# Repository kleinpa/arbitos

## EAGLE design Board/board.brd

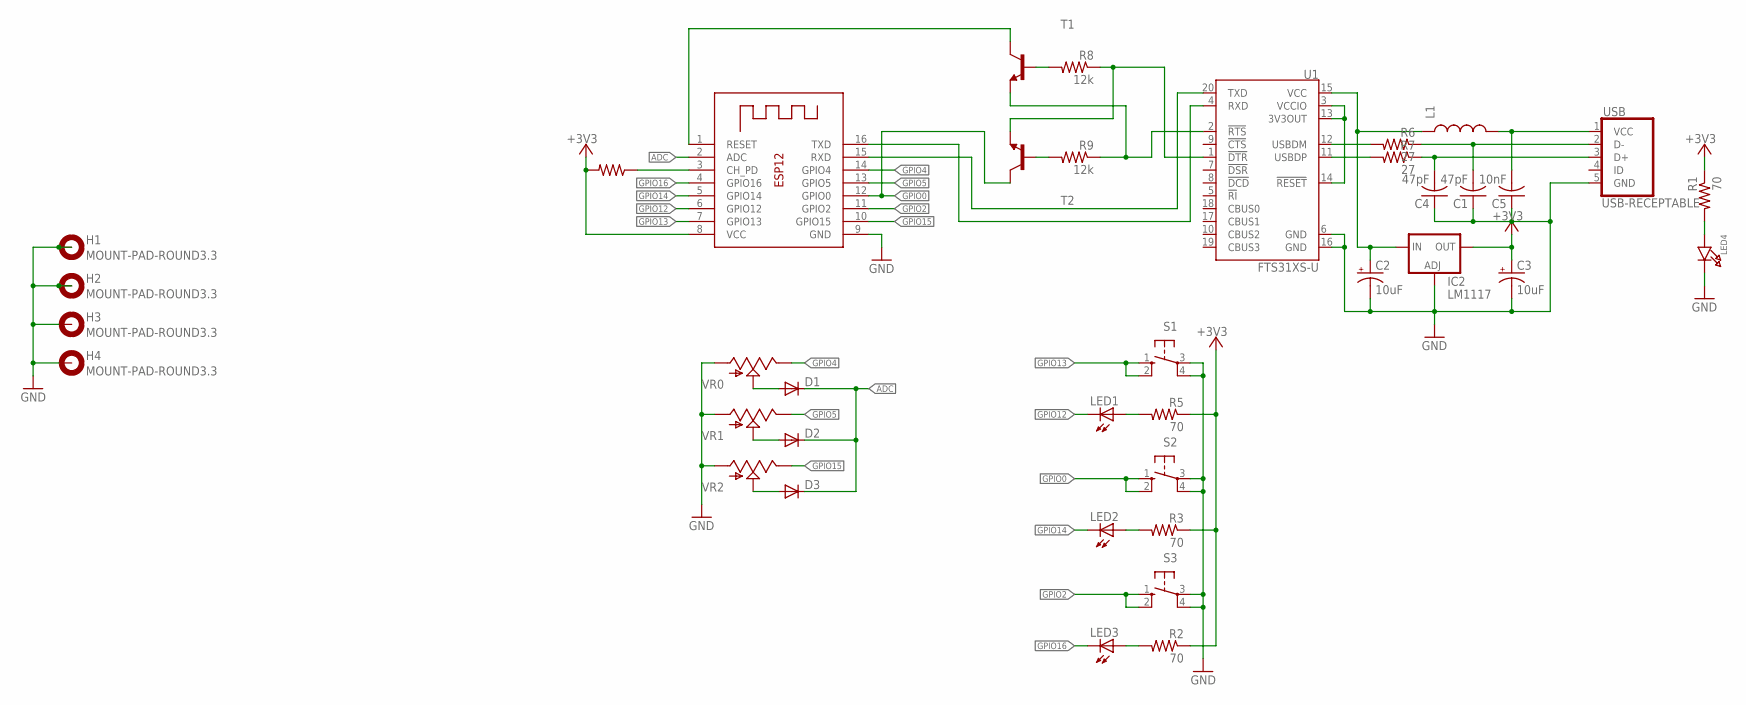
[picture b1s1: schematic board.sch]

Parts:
C1, C4: 47pF; C0603
C2, C3: 10uF; 153CLV-0405
C5: 10nF; C0603
D1, D2, D3: DIODE-DO214AC; DO214AC
H1, H2, H3, H4: MOUNT-PAD-ROUND3.3; 3,3-PAD
IC2: LM1117; DPACK
L1: INDUCTOR0805; 0805
LED1, LED2, LED3: LED3MM
LED4: LED0805; CHIPLED_0805
R1, R2, R3, R5: 70; R0603
R4: 10k; R0603
R6, R7: 27; R0603
R8, R9: 12k; R0603
S1, S2, S3: 10-XX; B3F-10XX
T1, T2: MMBT918LT1-NPN-SOT23-BEC; SOT23-BEC
U1: FTS31XS-U; SSOP20_L
USB: USB-RECEPTABLE; FCI-10103594-0001LF
VR0, VR1, VR2: SLIDERPTA3043; PTA3043-2015CPB103
X1: ESP-12

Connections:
+3V3: C3.+, IC2.4 (OUT), R1.1, R2.1, R3.1, R4.2, R5.1, X1.8 (VCC)
ADC: D1.C, D2.C, D3.C, X1.2 (ADC)
GND: C1.1, C2.-, C3.-, C4.1, C5.1, H1.B3,3, H2.B3,3, H3.B3,3, H4.B3,3, IC2.1 (ADJ), LED4.C, S1.3, S1.4 (P1), S2.3, S2.4 (P1), S3.3, S3.4 (P1), U1.6 (GND), U1.16 (GND), USB.5 (GND), VR0.P$1 (A), VR1.P$1 (A), VR2.P$1 (A), X1.9 (GND)
GPIO0: S2.1 (S), S2.2 (S1), T2.C, X1.12 (GPIO0)
GPIO2: S3.1 (S), S3.2 (S1), X1.11 (GPIO2)
GPIO4: VR0.P$3 (E), X1.14 (GPIO4)
GPIO5: VR1.P$3 (E), X1.13 (GPIO5)
GPIO12: LED1.K (C), X1.6 (GPIO12)
GPIO13: S1.1 (S), S1.2 (S1), X1.7 (GPIO13)
GPIO14: LED2.K (C), X1.5 (GPIO14)
GPIO15: VR2.P$3 (E), X1.10 (GPIO15)
GPIO16: LED3.K (C), X1.4 (GPIO16)
unnamed: R4.1, X1.3 (CH_PD)
unnamed: C4.2, R7.1, USB.3 (D+)
unnamed: R7.2, U1.11 (USBDP)
unnamed: LED4.A, R1.2
unnamed: D1.A, VR0.P$2 (S)
unnamed: LED1.A, R5.2
unnamed: C5.2, L1.2, USB.1 (VCC)
unnamed: LED2.A, R3.2
unnamed: R6.2, U1.12 (USBDM)
unnamed: LED3.A, R2.2
unnamed: D2.A, VR1.P$2 (S)
unnamed: D3.A, VR2.P$2 (S)
unnamed: C1.2, R6.1, USB.2 (D-)
unnamed: R8.1, T2.E, U1.1 (!DTR)
unnamed: R9.1, T1.E, U1.2 (!RTS)
unnamed: R8.2, T1.B
unnamed: R9.2, T2.B
unnamed: U1.3 (VCCIO), U1.13 (3V3OUT), U1.14 (!RESET)
unnamed: C2.+, IC2.3 (IN), L1.1, U1.15 (VCC)
RST: T1.C, X1.1 (RESET)
RXI: U1.20 (TXD), X1.15 (RXD)
TXO: U1.4 (RXD), X1.16 (TXD)

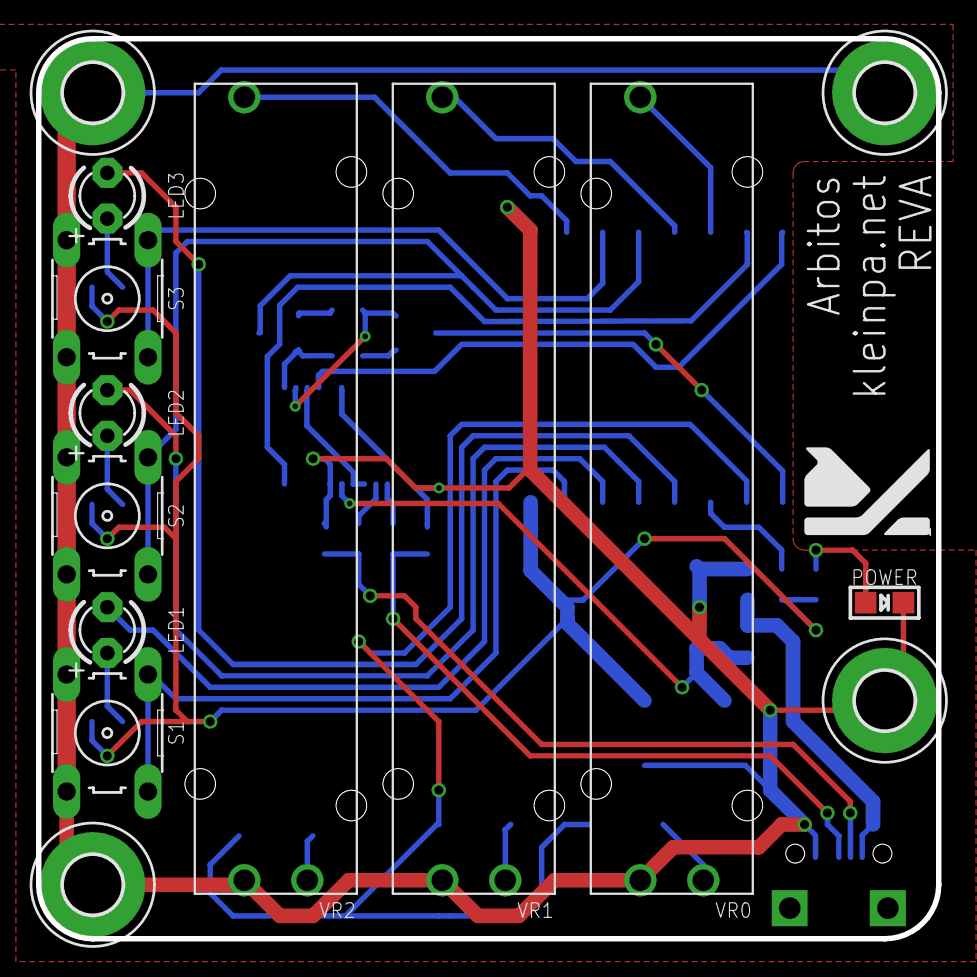
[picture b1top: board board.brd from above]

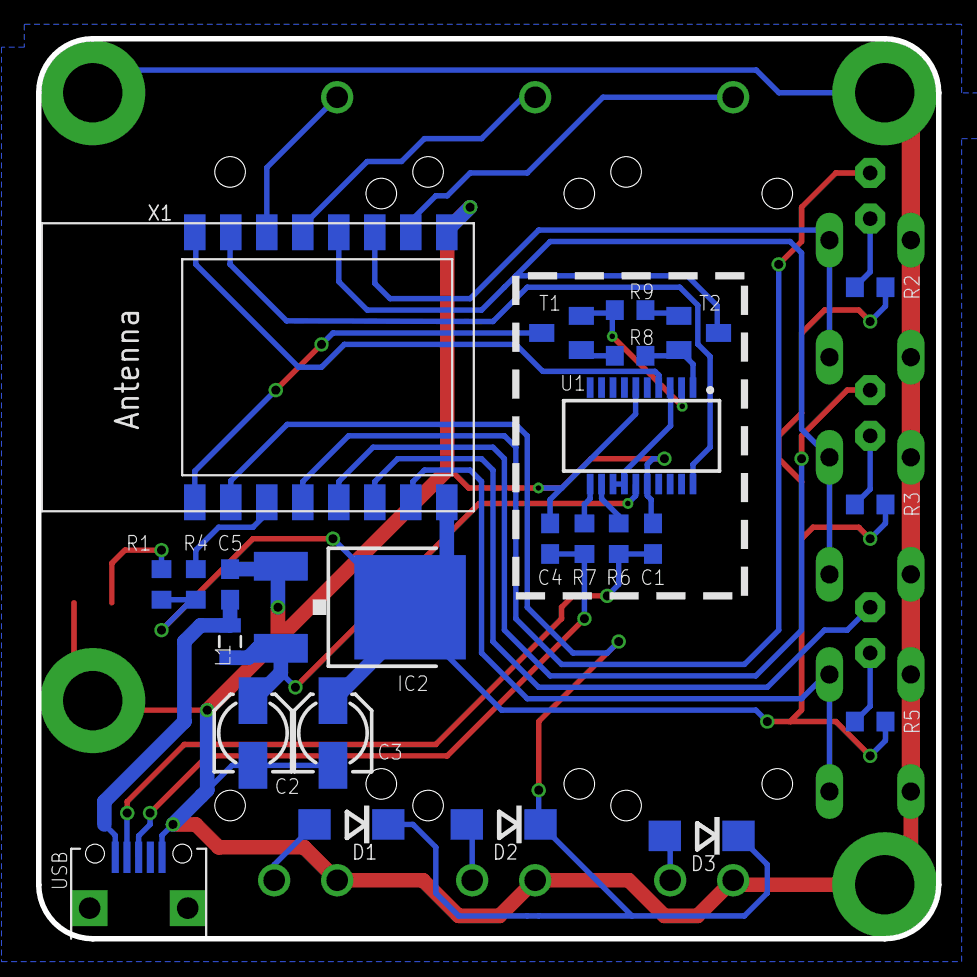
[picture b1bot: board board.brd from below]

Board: 2 copper layers, 50.0 x 50.0 mm, 38 parts (24 on the bottom side), 34 nets.

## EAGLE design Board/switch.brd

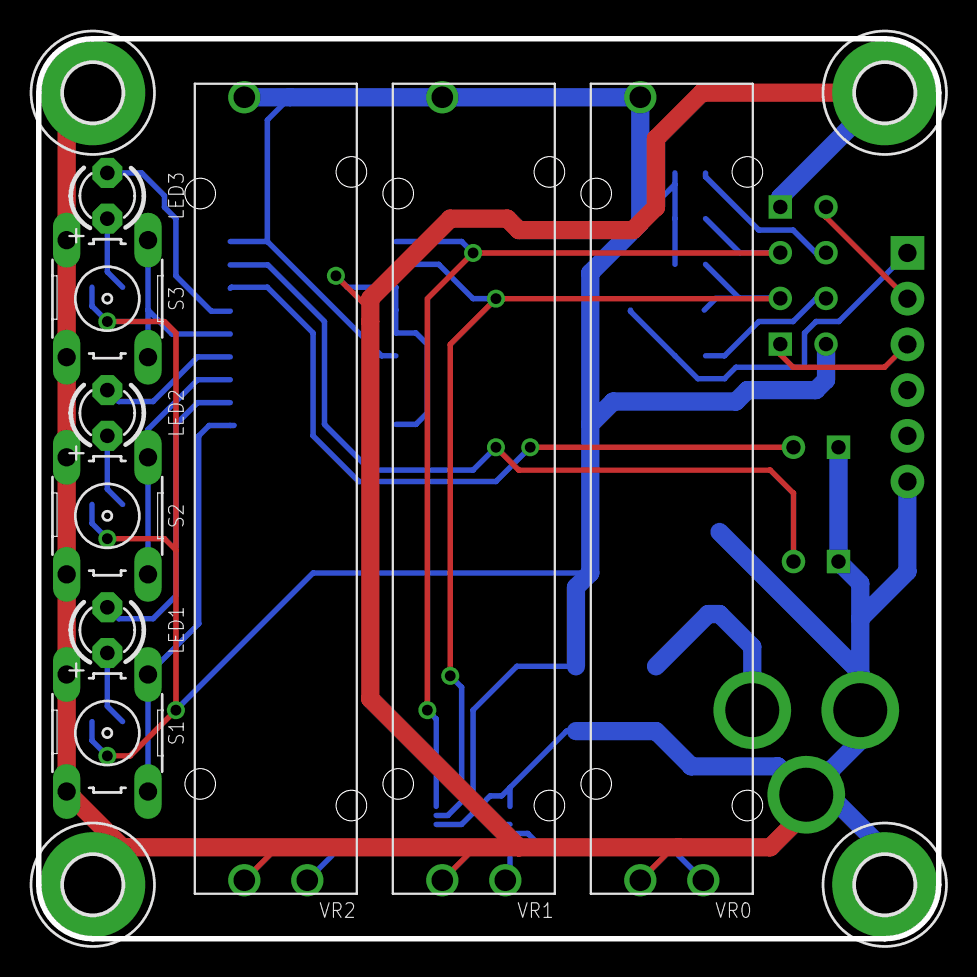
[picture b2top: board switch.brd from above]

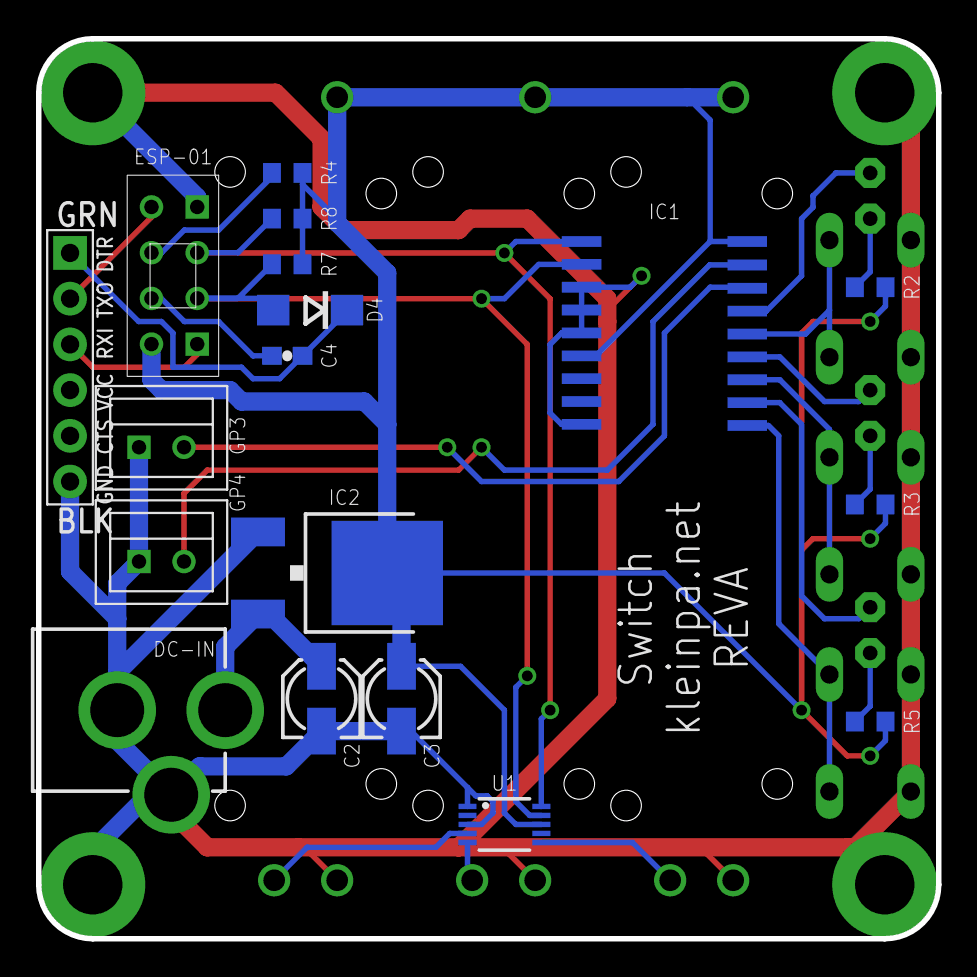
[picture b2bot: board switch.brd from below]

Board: 2 copper layers, 50.0 x 50.0 mm, 31 parts (18 on the bottom side), 24 nets.

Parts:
C2, C3: 10uF; 153CLV-0405
C4: .1uF; 0603-CAP
D4: DO214AC
DC-IN: POWER_JACKPTH; POWER_JACK_PTH
ESP-01: ESP01
GP3, GP4: 02-JST; B2B-XH
H1, H2, H3, H4: MOUNT-PAD-ROUND3.3; 3,3-PAD
IC1: MCP2300X/SO; SO18W
IC2: LM1117; DPACK
JP2: FTDI_DEVICE; FTDI_DEVICE_SIDE
LED1, LED2, LED3: LED3MM
R2, R3, R5: 70; R0603
R4, R7, R8: 10k; R0603
S1, S2, S3: B3F-10XX
U1: ADS1015; MSOP10
VR0, VR1, VR2: PTA3043-2015CPB103

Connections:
+3V3: C3.+, ESP-01.VCC, IC1.6, IC1.18, IC2.4, R2.1, R3.1, R4.2, R5.1, R7.2, R8.2, U1.8, VR0.P$3, VR1.P$3, VR2.P$3
GND: C2.-, C3.-, DC-IN.GND, DC-IN.GNDBREAK, ESP-01.GND, GP3.P$1, GP4.P$1, H1.B3,3, H2.B3,3, H3.B3,3, H4.B3,3, IC1.3, IC1.4, IC1.5, IC1.9, IC2.1, JP2.P$6, S1.3, S1.4, S2.3, S2.4, S3.3, S3.4, U1.1, U1.3, VR0.P$1, VR1.P$1, VR2.P$1
GP0: IC1.10, S1.1, S1.2
GP1: IC1.11, LED1.K
GP2: IC1.12, S2.1, S2.2
GP3: IC1.13, LED2.K
GP4: IC1.14, S3.1, S3.2
GP5: IC1.15, LED3.K
GP6: GP3.P$2, IC1.16
GP7: GP4.P$2, IC1.17
I2C_SCL: ESP-01.GPIO2, IC1.1, R8.1, U1.10
I2C_SDA: D4.A, ESP-01.GPIO0, IC1.2, R7.1, U1.9
unnamed: ESP-01.CH_PD, R4.1
unnamed: C4.2, D4.C, JP2.P$1
unnamed: U1.6, VR2.P$2
unnamed: U1.5, VR1.P$2
unnamed: U1.4, VR0.P$2
unnamed: LED1.A, R5.2
unnamed: LED2.A, R3.2
unnamed: LED3.A, R2.2
RST: C4.1, ESP-01.RST
RXI: ESP-01.RX, JP2.P$3
TXO: ESP-01.TX, JP2.P$2
VCC: C2.+, DC-IN.PWR, IC2.3

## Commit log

2016-01-10 Add first pass board component layout
2016-01-10 Use PTA3043 footprint for slider
2016-01-10 Use pcb-mount buttons
2016-01-15 Route traces and tweak layout
2016-01-16 Rename project
2016-01-22 Use cheaper ADC and add LEDs on spare GPIO
2016-01-30 Proof of concept hue control
2016-02-02 Create Hue class and use HTTPClient
2016-02-28 Finish routing PCB
2016-03-14 Add mDNS, unique hostnames, and fix EEPROM id check
2016-03-14 Hack a proof of concept together
2016-03-15 Add hardware abstraction library
2016-03-15 Move network stuff into own module
    Eventually access-point fallback and OTA programming will be added here
2016-03-15 Take a pass at using a fallback wifi AP
2016-03-16 Add setOff and setRGB to hue api

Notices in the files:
parts and their libraries:
SparkFun-Electromechanical: Licensing: Creative Commons ShareAlike 4.0 International - https://creativecommons.org/licenses/by-sa/4.0
